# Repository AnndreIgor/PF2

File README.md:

# PF2
Projeto com os arquivos utilizados na construção do sistema para monitoramento do datacenter para o CEFET/RJ UNED NI

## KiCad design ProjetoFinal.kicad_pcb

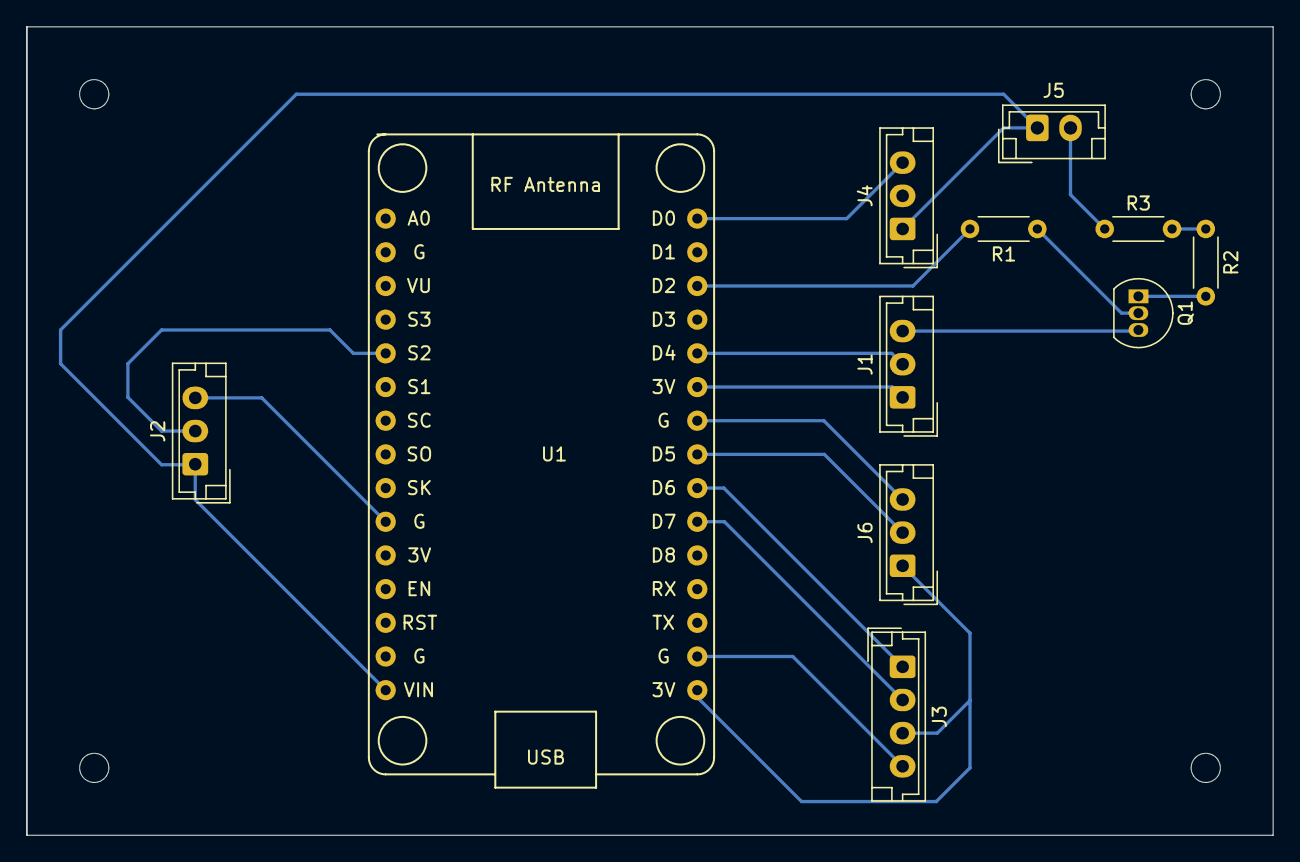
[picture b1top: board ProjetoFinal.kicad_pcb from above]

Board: 2 copper layers, 94.0 x 61.0 mm, 15 parts (0 on the bottom side), 14 nets.

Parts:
H1, H2, H3, H4: MountingHole_2.2mm_M2
J1: DS18B20; JST_EH_B3B-EH-A_1x03_P2.50mm_Vertical
J2: HC-SR501; JST_EH_B3B-EH-A_1x03_P2.50mm_Vertical
J3: Conn_01x04; JST_EH_B4B-EH-A_1x04_P2.50mm_Vertical
J4: RELE; JST_EH_B3B-EH-A_1x03_P2.50mm_Vertical
J5: LED_IR; JST_EH_B2B-EH-A_1x02_P2.50mm_Vertical
J6: MQ-2; JST_EH_B3B-EH-A_1x03_P2.50mm_Vertical
Q1: BC547; TO-92_Inline
R1: 10K; R_Axial_DIN0204_L3.6mm_D1.6mm_P5.08mm_Horizontal
R2: 22R; R_Axial_DIN0204_L3.6mm_D1.6mm_P5.08mm_Horizontal
R3: 4,7R; R_Axial_DIN0204_L3.6mm_D1.6mm_P5.08mm_Horizontal
U1: NodeMCU1.0(ESP-12E); ESP12F-Devkit-V3

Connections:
/3V3: J1.1, J3.3, J6.1, U1.11 (3.3V), U1.16 (3.3V), U1.25 (3.3V)
/D0(GIPIO16): J4.3, U1.30 (D0(GPIO16))
/D2(GPIO4): R1.2, U1.28 (D2(GPIO4))
/D4(GPIO2): J1.2, U1.26 (D4(GPIO2))
/D5(GIPIO14): J6.2, U1.23 (D5(GPIO14))
/D6(GPIO12): J3.1, U1.22 (D6(GPIO12))
/D7(GPIO13): J3.2, U1.21 (D7(GPIO13))
/GND: J1.3, J2.3, J3.4, J4.2, J6.3, Q1.3 (E), U1.10 (GND), U1.14 (GND), U1.17 (GND), U1.24 (GND)
/SD2(GPIO9): J2.2, U1.5 (SD2(GPIO9))
/VIN: J2.1, J4.1, J5.1, U1.15 (VIN)
unnamed: J5.2, R3.1
unnamed: Q1.1 (C), R2.2
unnamed: Q1.2 (B), R1.1
unnamed: R2.1, R3.2

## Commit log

2022-08-08 Skecth do arduino IDE
